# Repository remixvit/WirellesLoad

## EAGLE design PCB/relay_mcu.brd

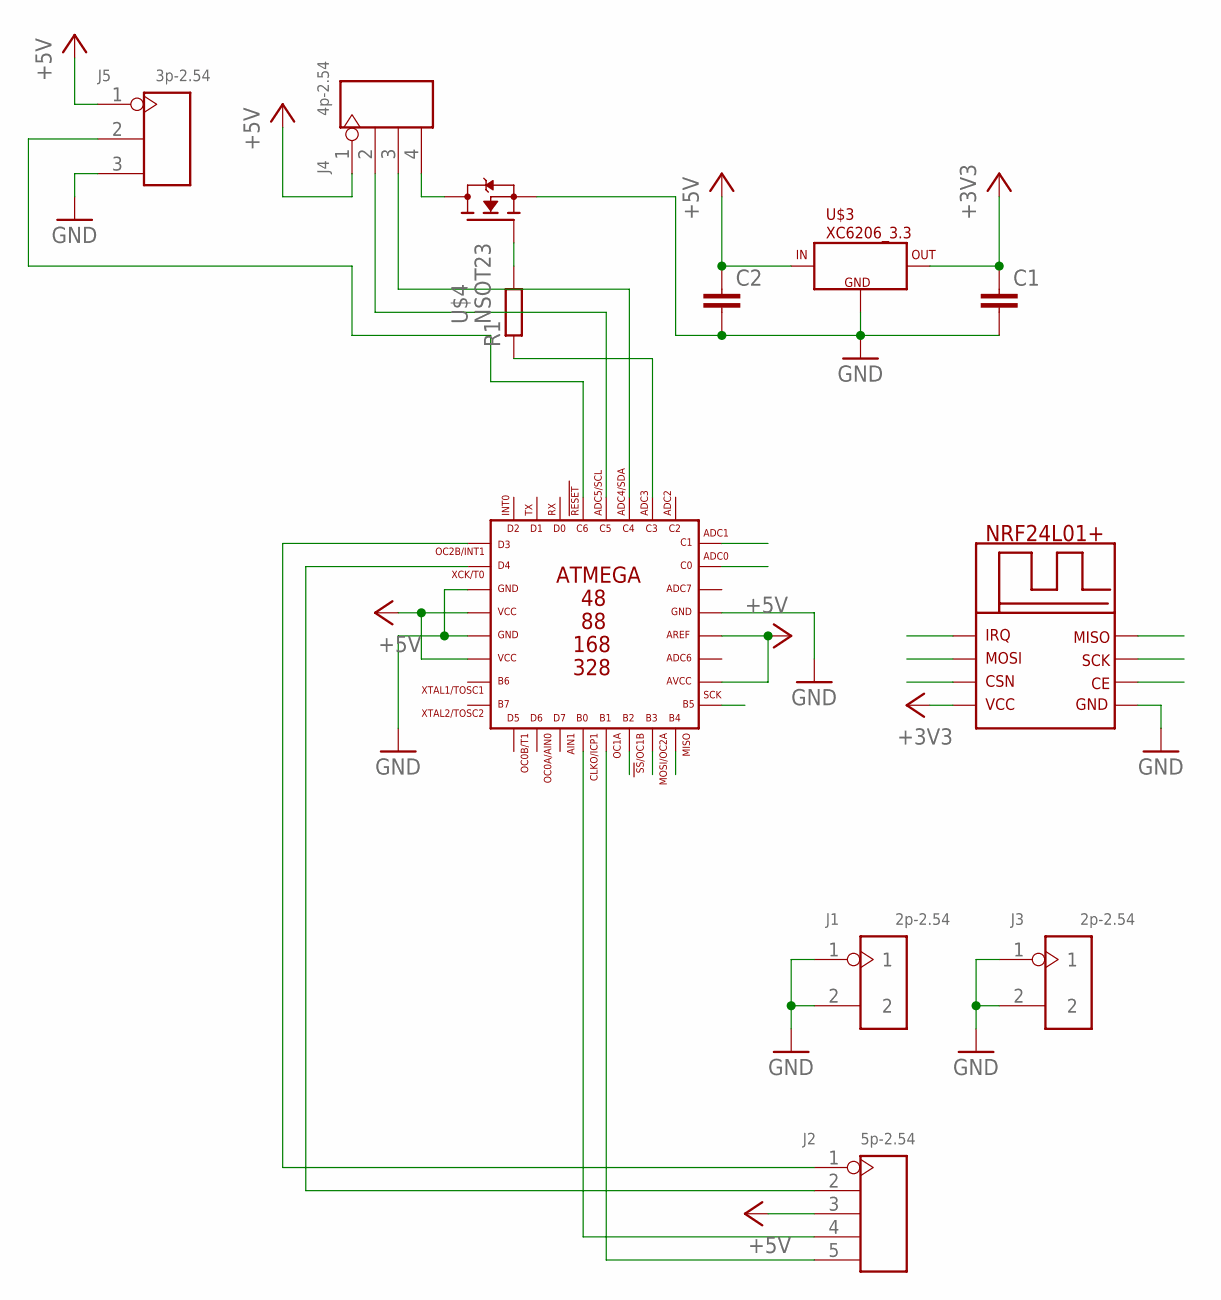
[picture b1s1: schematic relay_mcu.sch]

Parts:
C1, C2: C-EUC0805; C0805
J1, J3: 2p-2.54; H2-2.54
J2: 5p-2.54; H5-2.54
J4: 4p-2.54; H4-2.54
J5: 3p-2.54; H3-2.54
R1: R-EU_R0805; R0805
U$1: ATMEGAN8; TQFP32-08
U$2: NRF24; NRF
U$3: XC6206_3.3; SOT23
U$4: NSOT23; SOT23W

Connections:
+3V3: C1.1, U$2.VCC, U$3.2 (OUT)
+5V: J4.1, J5.1
CE: U$1.C1, U$2.CE
CSN: U$1.C0, U$2.CSN
GND: C1.2, C2.2, J1.1, J1.2, J3.1, J3.2, J5.3, U$1.GND, U$1.GND1, U$1.GND2, U$2.GND, U$3.1 (GND), U$4.S
IRQ: U$1.B2, U$2.IRQ
MISO: U$1.B4, U$2.MISO
MOSI: U$1.B3, U$2.MOSI
unnamed: C2.1, J2.3, U$1.AREF, U$1.AVCC, U$1.VCC, U$1.VCC1, U$3.3 (IN)
unnamed: J2.5, U$1.B1
unnamed: J2.4, U$1.B0
unnamed: J2.1, U$1.D3
unnamed: J2.2, U$1.D4
unnamed: J4.2, U$1.C5
unnamed: J4.3, U$1.C4
unnamed: J4.4, U$4.D
unnamed: R1.2, U$4.G
unnamed: R1.1, U$1.C3
unnamed: J5.2, U$1.C6
SCLK: U$1.B5, U$2.SCK

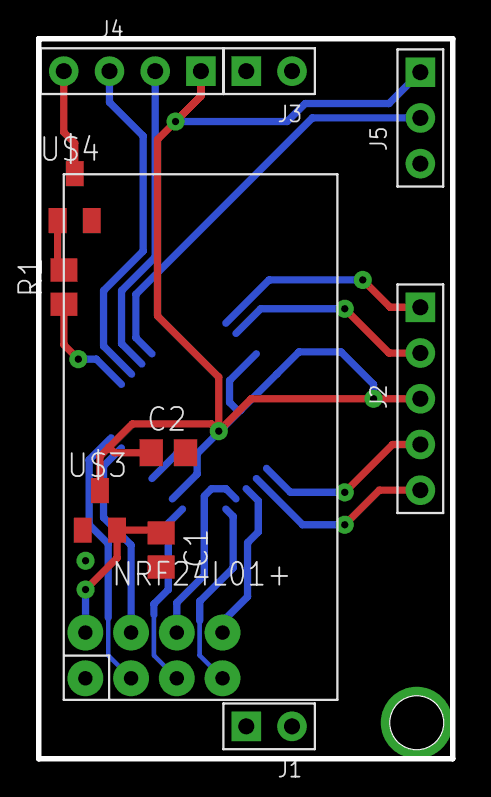
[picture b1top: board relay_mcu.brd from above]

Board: 2 copper layers, 23.0 x 40.0 mm, 12 parts (1 on the bottom side), 20 nets.

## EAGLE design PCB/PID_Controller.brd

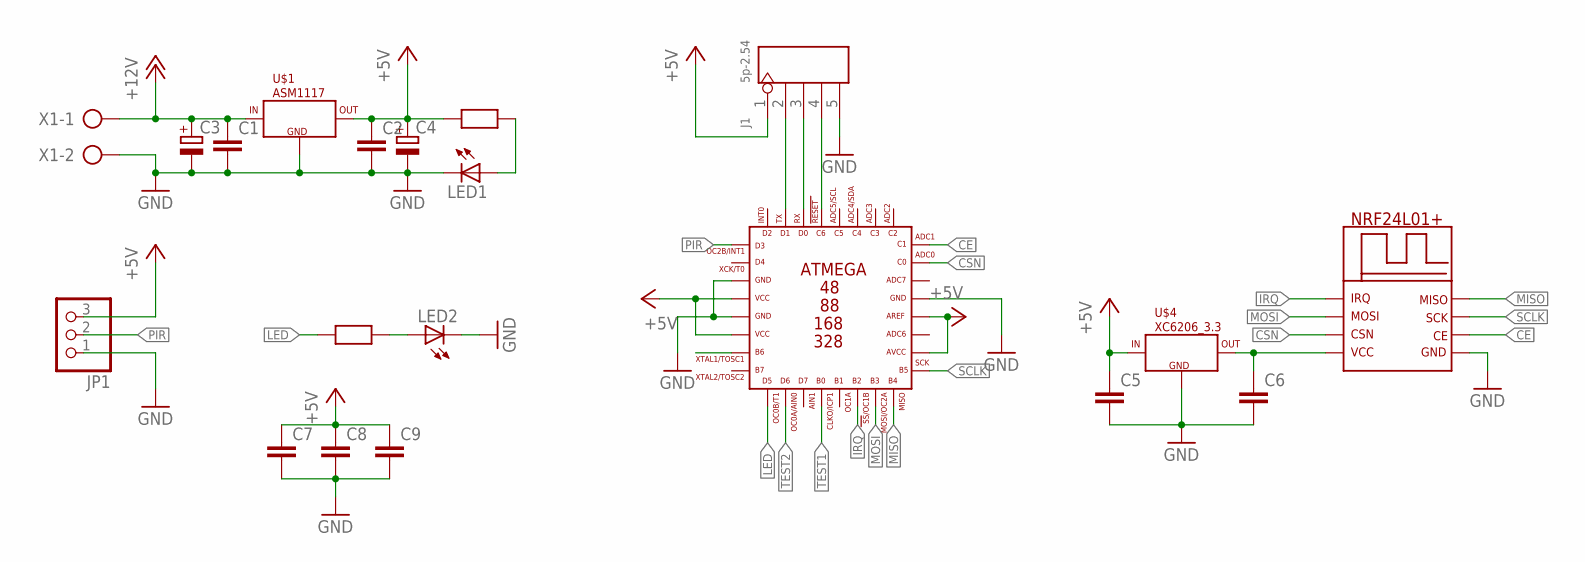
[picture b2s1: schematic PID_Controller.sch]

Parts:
C1, C2, C5, C6, C7, C8, C9: C-EUC0805; C0805
C3, C4: CPOL-EUE2.5-6; E2,5-6
J1: 5p-2.54; H5-2.54
JP1: PINHD-1X3; 1X03
LED1: LEDCHIP-LED0603; CHIP-LED0603
LED2: LED3MM
R1, R2: RES0603; R0603
U$1: ASM1117; SOT223
U$2: ATMEGAN8; TQFP32-08
U$3: NRF24; NRF
U$4: XC6206_3.3; SOT23
X1: AK500/2

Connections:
+5V: C2.1, C4.+, C5.1, C7.1, C8.1, C9.1, J1.1, JP1.3, R1.1, U$1.2 (OUT), U$1.4 (OUT), U$2.AREF, U$2.AVCC, U$2.VCC, U$2.VCC1, U$4.3 (IN)
+12V: C1.1, C3.+, U$1.3 (IN), X1.1
CE: U$2.C1, U$3.CE
CSN: U$2.C0, U$3.CSN
GND: C1.2, C2.2, C3.-, C4.-, C5.2, C6.2, C7.2, C8.2, C9.2, J1.5, JP1.1, LED1.C, LED2.K (C), U$1.1 (GND), U$2.GND, U$2.GND1, U$2.GND2, U$3.GND, U$4.1 (GND), X1.2
IRQ: U$2.B2, U$3.IRQ
LED: R2.1, U$2.D5
MISO: U$2.B4, U$3.MISO
MOSI: U$2.B3, U$3.MOSI
unnamed: LED1.A, R1.2
unnamed: J1.2, U$2.D1
unnamed: J1.3, U$2.D0
unnamed: J1.4, U$2.C6
unnamed: C6.1, U$3.VCC, U$4.2 (OUT)
unnamed: LED2.A, R2.2
PIR: JP1.2, U$2.D3
SCLK: U$2.B5, U$3.SCK
TEST1: U$2.B0
TEST2: U$2.D6

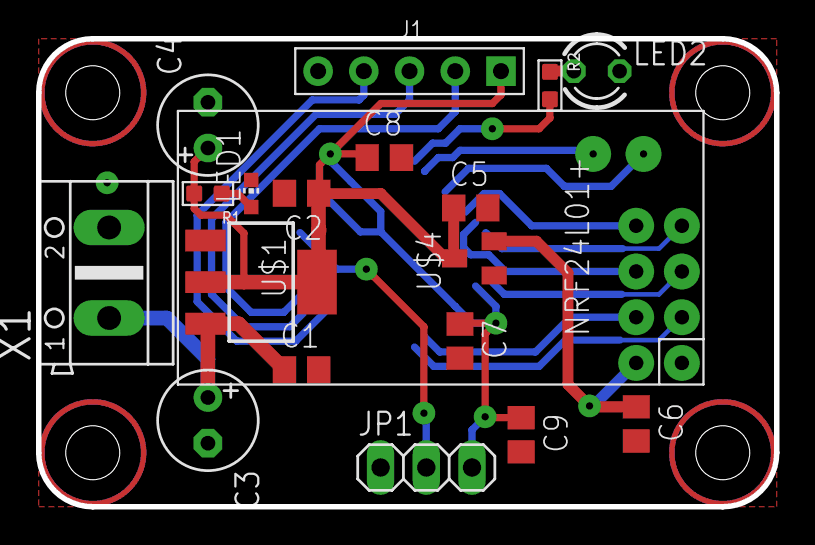
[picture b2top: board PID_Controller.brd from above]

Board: 2 copper layers, 41.0 x 26.0 mm, 20 parts (1 on the bottom side), 17 nets.

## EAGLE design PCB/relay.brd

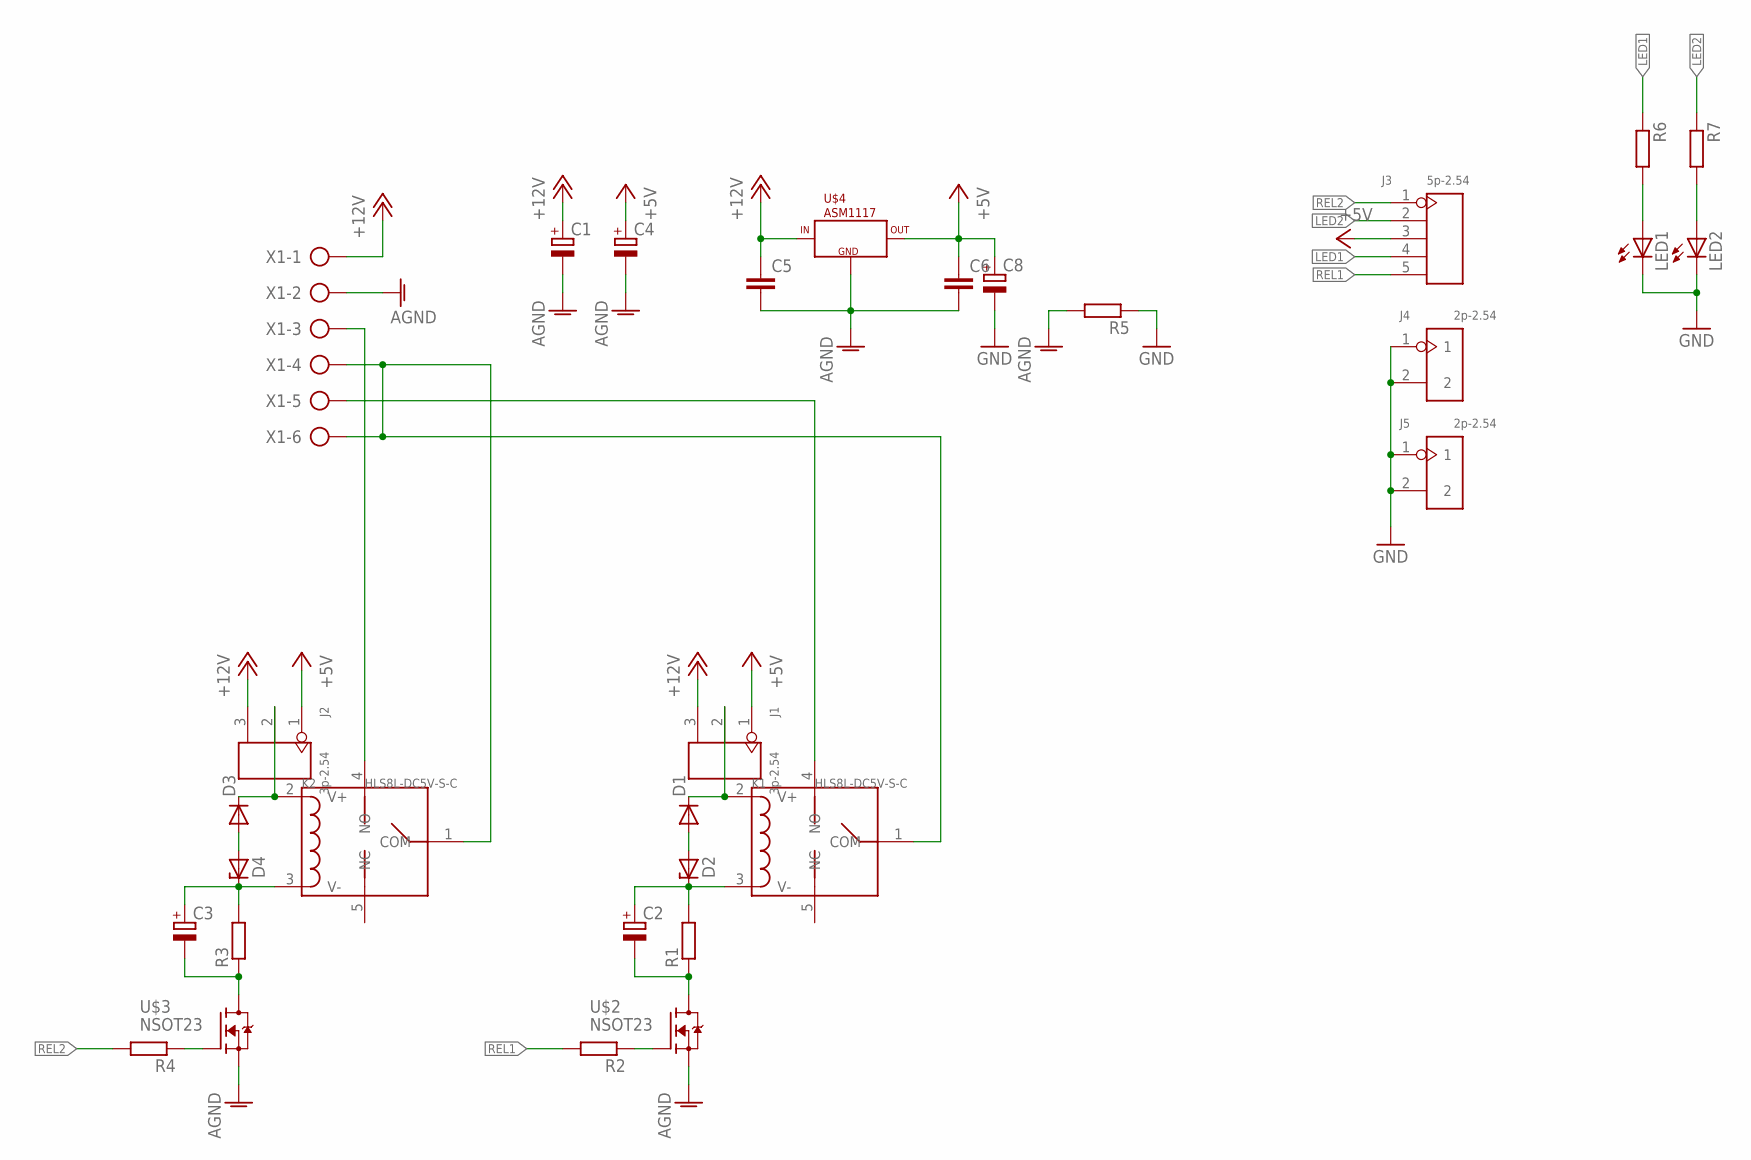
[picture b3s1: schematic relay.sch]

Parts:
C1, C2, C3, C4: CPOL-EU153CLV-0405; 153CLV-0405
C5, C6: C-EUC0805; C0805
C8: CPOL-EUSMCD; SMC_D
D1, D3: DIODE-MINIMELF; MINIMELF
D2, D4: ZENER-DIODESOD80C; SOD80C
J1, J2: 3p-2.54; H3-2.54
J3: 5p-2.54; H5-2.54
J4, J5: 2p-2.54; H2-2.54
K1, K2: HLS8L-DC5V-S-C; REY5-19.0X15.0X15.0MM
LED1, LED2: LED5MM
R1, R2, R3, R4, R5, R6, R7: R-EU_R0805; R0805
U$2, U$3: NSOT23; SOT23W
U$4: ASM1117; SOT223
X1: AK500/6-H

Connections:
+5V: C4.+, C6.1, C8.+, J1.1, J2.1, J3.3, U$4.2 (OUT), U$4.4 (OUT)
+12V: C1.+, C5.1, J1.3, J2.3, U$4.3 (IN), X1.1
AGND: C1.-, C4.-, C5.2, C6.2, R5.2, U$2.S, U$3.S, U$4.1 (GND), X1.2
GND: C8.-, J4.1, J4.2, J5.1, J5.2, LED1.K (C), LED2.K (C), R5.1
LED1: J3.4, R6.1
LED2: J3.2, R7.1
unnamed: D1.C, J1.2, K1.2 (V+)
unnamed: C2.+, D2.C, K1.3 (V-), R1.2
unnamed: D1.A, D2.A
unnamed: C2.-, R1.1, U$2.D
unnamed: R2.1, U$2.G
unnamed: K1.4 (NO), X1.5
unnamed: D3.C, J2.2, K2.2 (V+)
unnamed: C3.+, D4.C, K2.3 (V-), R3.2
unnamed: D3.A, D4.A
unnamed: C3.-, R3.1, U$3.D
unnamed: R4.1, U$3.G
unnamed: LED1.A, R6.2
unnamed: K1.1 (COM), K2.1 (COM), X1.4, X1.6
unnamed: LED2.A, R7.2
unnamed: K2.4 (NO), X1.3
REL1: J3.5, R2.2
REL2: J3.1, R4.2

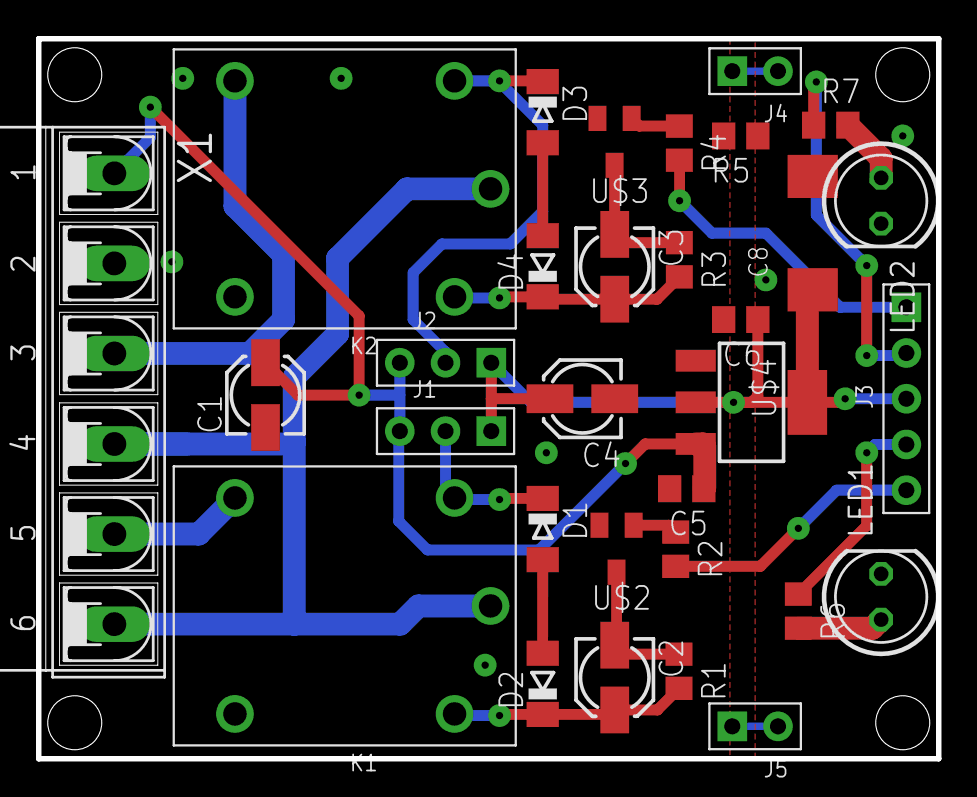
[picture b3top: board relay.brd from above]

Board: 2 copper layers, 50.0 x 40.0 mm, 31 parts (0 on the bottom side), 23 nets.

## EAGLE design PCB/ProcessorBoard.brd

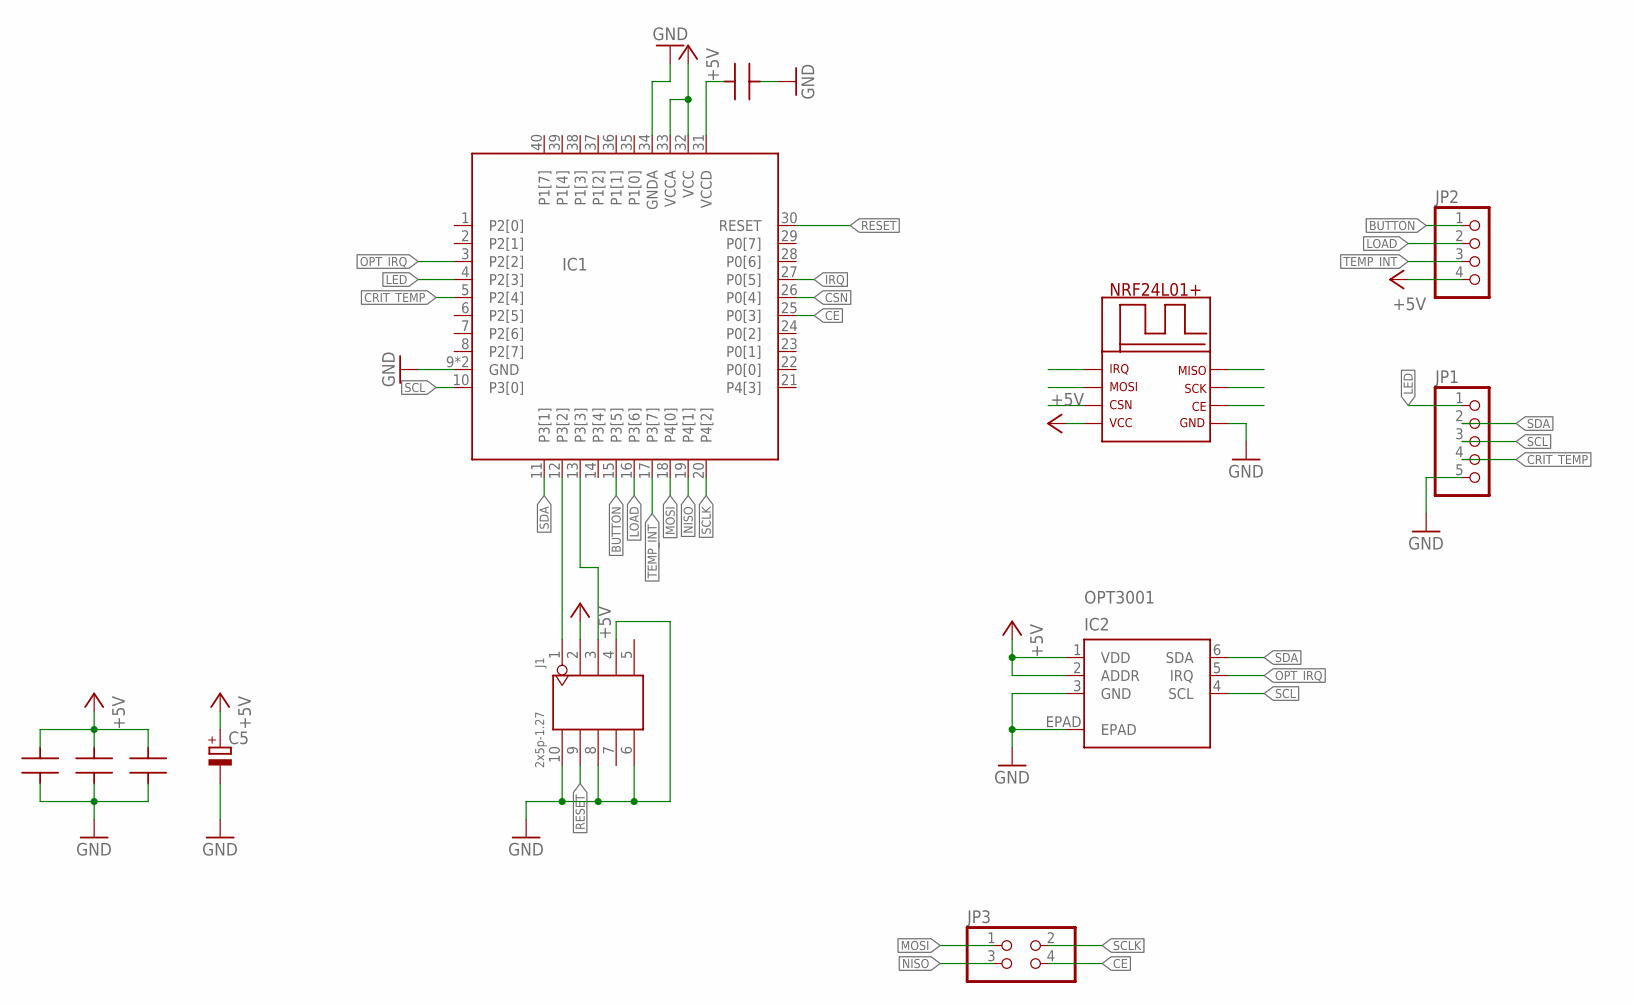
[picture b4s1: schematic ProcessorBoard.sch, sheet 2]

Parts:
C1, C2, C3, C4: CAP0603; C0603
C5: CPOL-EUSMCA; SMC_A
IC1: CY8C4245-LQI-LONG; QFN40-LONG
IC2: OPT3001; USON6
J1: 2x5p-1.27; H2X5-SMD-1.27
JP1: PINHD-1X5; 1X05
JP2: PINHD-1X4; 1X04
JP3: PINHD-2X2; 2X02
U$1: NRF24; NRF

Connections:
+5V: C2.2, C3.2, C4.2, C5.+, IC1.32 (VCC), IC1.33 (VCCA), IC2.1 (VDD), IC2.2 (ADDR), J1.2, JP2.4, U$1.VCC
BUTTON: IC1.15 (P3[5]), JP2.1
CE: IC1.25 (P0[3]), JP3.4, U$1.CE
CRIT_TEMP: IC1.5 (P2[4]), JP1.4
CSN: IC1.26 (P0[4]), U$1.CSN
GND: C1.2, C2.1, C3.1, C4.1, C5.-, IC1.9 (GND), IC1.34 (GNDA), IC1.41 (GND), IC2.3 (GND), IC2.EPAD, J1.4, J1.6, J1.8, J1.10, JP1.5, U$1.GND
IRQ: IC1.27 (P0[5]), U$1.IRQ
LED: IC1.4 (P2[3]), JP1.1
LOAD: IC1.16 (P3[6]), JP2.2
MOSI: IC1.18 (P4[0]), JP3.1, U$1.MOSI
unnamed: IC1.12 (P3[2]), J1.1
unnamed: C1.1, IC1.31 (VCCD)
unnamed: IC1.13 (P3[3]), J1.3
NISO: IC1.19 (P4[1]), JP3.3, U$1.MISO
OPT_IRQ: IC1.3 (P2[2]), IC2.5 (IRQ)
RESET: IC1.30 (RESET), J1.9
SCL: IC1.10 (P3[0]), IC2.4 (SCL), JP1.3
SCLK: IC1.20 (P4[2]), JP3.2, U$1.SCK
SDA: IC1.11 (P3[1]), IC2.6 (SDA), JP1.2
TEMP_INT: IC1.17 (P3[7]), JP2.3

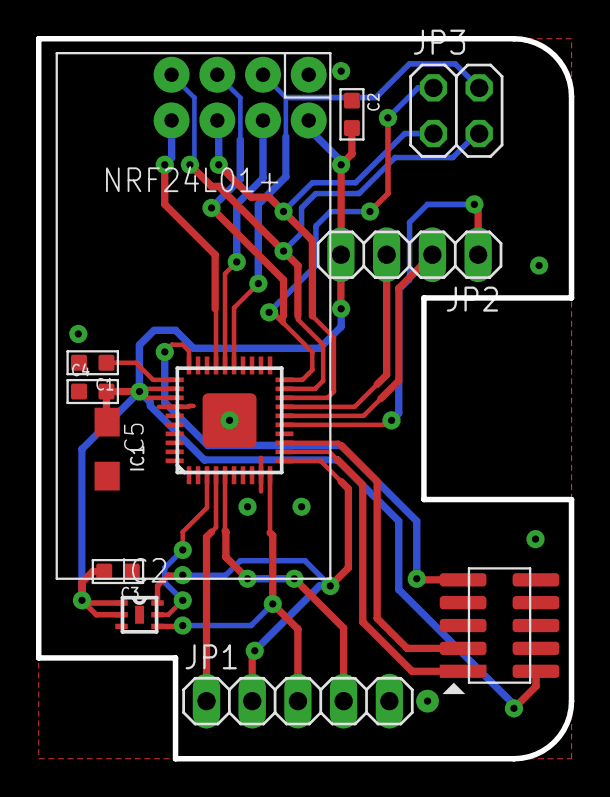
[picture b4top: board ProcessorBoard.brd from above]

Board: 2 copper layers, 29.6 x 40.0 mm, 12 parts (0 on the bottom side), 20 nets.

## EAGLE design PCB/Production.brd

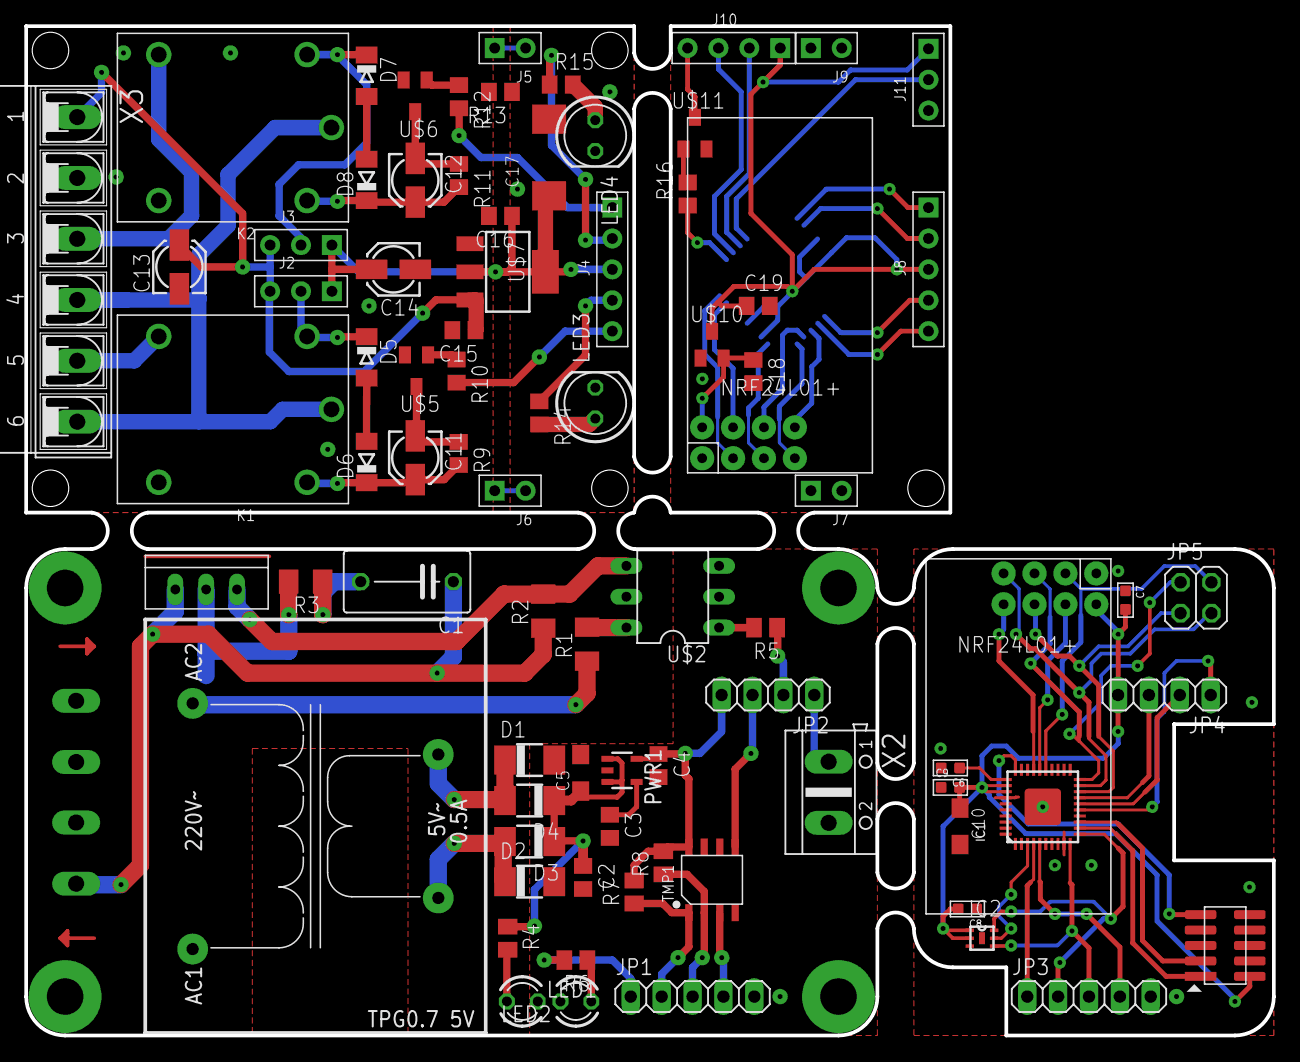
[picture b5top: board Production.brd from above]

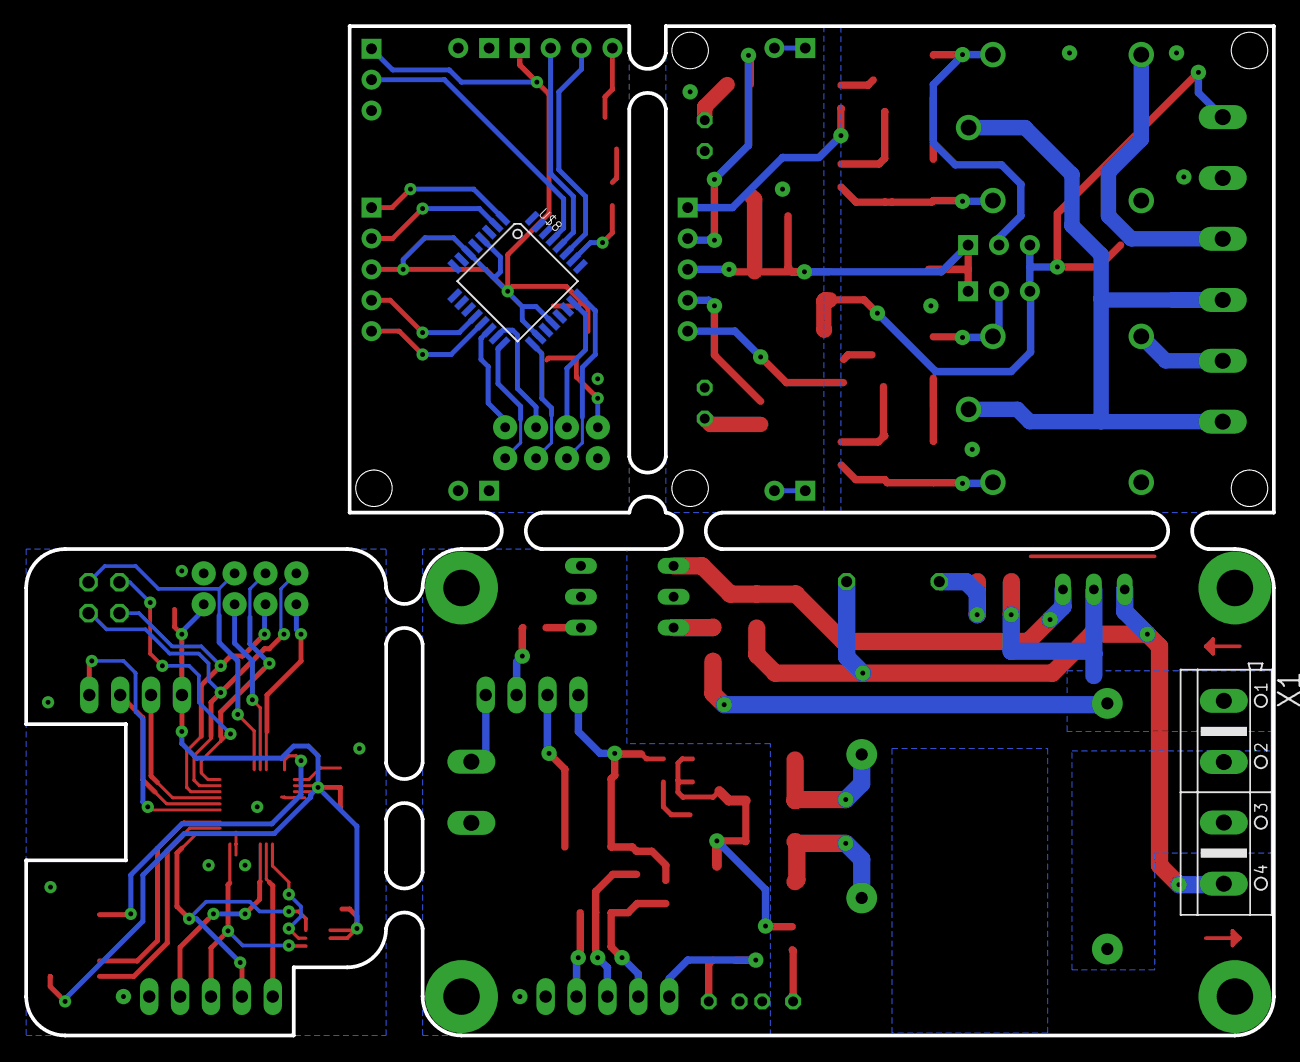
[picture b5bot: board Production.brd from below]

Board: 2 copper layers, 102.6 x 83.0 mm, 83 parts (2 on the bottom side), 85 nets.

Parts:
C1: C075-052X106
C2, C3, C4, C15, C16, C18, C19: C0805
C5, C10: SMC_A
C6, C7, C8, C9: C0603
C11, C12, C13, C14: 153CLV-0405
C17: SMC_D
D1, D2, D3, D4: DO-214AC
D5, D7: MINIMELF
D6, D8: SOD80C
IC1: CY8C4245-LQI-LONG; QFN40-LONG
IC2: OPT3001; USON6
J1: 2x5p-1.27; H2X5-SMD-1.27
J2, J3, J11: 3p-2.54; H3-2.54
J4, J8: 5p-2.54; H5-2.54
J5, J6, J7, J9: 2p-2.54; H2-2.54
J10: 4p-2.54; H4-2.54
JP1, JP3: 1X05
JP2, JP4: 1X04
JP5: 2X02
K1, K2: HLS8L-DC5V-S-C; REY5-19.0X15.0X15.0MM
LED1, LED2: LED3MM
LED3, LED4: LED5MM
PWR1: LP2992; SOT23-5
R1, R2, R3: M1206
R4, R5, R6, R7, R8: M0805
R9, R10, R11, R12, R13, R14, R15, R16: R0805
TMP1: LM92; SOIC8-1.27-5X4MM
U$1: ТПГ-0.7-5V; TPG-0.7-5V
U$2: MOC3043; DIL06
U$3: BTB16; TO220NORM
U$4, U$9: NRF24; NRF
U$5, U$6, U$11: NSOT23; SOT23W
U$7: ASM1117; SOT223
U$8: ATMEGAN8; TQFP32-08
U$10: XC6206_3.3; SOT23
X1: AK500/4
X2: AK500/2
X3: AK500/6-H

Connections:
+3V3: C18.1, U$9.VCC, U$10.2
+5V: C4.1, JP2.4, PWR1.5, R7.2, R8.2, TMP1.8
+5V1: C7.2, C8.2, C9.2, C10.+, IC1.32, IC1.33, IC2.1, IC2.2, J1.2, JP4.4, U$4.VCC
+5V2: C14.+, C16.1, C17.+, J2.1, J3.1, J4.3, U$7.2, U$7.4
+5V3: J10.1, J11.1
+12V: C13.+, C15.1, J2.3, J3.3, U$7.3, X3.1
AGND: C13.-, C14.-, C15.2, C16.2, R13.2, U$5.S, U$6.S, U$7.1, X3.2
BUTTON: IC1.15, JP4.1
CE: IC1.25, JP5.4, U$4.CE
CE1: U$8.C1, U$9.CE
CRIT_TEMP: IC1.5, JP3.4
CSN: IC1.26, U$4.CSN
CSN1: U$8.C0, U$9.CSN
GND: C2.2, C3.2, C4.2, C5.-, D1.A, D2.A, JP1.5, LED1.K, LED2.K, PWR1.2, TMP1.4, TMP1.6, TMP1.7, U$2.2, X2.2
GND1: C6.2, C7.1, C8.1, C9.1, C10.-, IC1.9, IC1.34, IC1.41, IC2.3, IC2.EPAD, J1.4, J1.6, J1.8, J1.10, JP3.5, U$4.GND
GND2: C17.-, J5.1, J5.2, J6.1, J6.2, LED3.K, LED4.K, R13.1
GND3: C18.2, C19.2, J7.1, J7.2, J9.1, J9.2, J11.3, U$8.GND, U$8.GND1, U$8.GND2, U$9.GND, U$10.1, U$11.S
IRQ: IC1.27, U$4.IRQ
IRQ1: U$8.B2, U$9.IRQ
LED: IC1.4, JP3.1
LED1: J4.4, R14.1
LED2: J4.2, R15.1
LOAD: JP2.2, R5.1
LOAD1: IC1.16, JP4.2
MISO: U$8.B4, U$9.MISO
MOSI: IC1.18, JP5.1, U$4.MOSI
MOSI1: U$8.B3, U$9.MOSI
unnamed: U$1.AC1, X1.2, X1.3
unnamed: R1.1, R3.2, U$1.AC2, U$3.MT2, X1.1
unnamed: D1.C, D4.A, U$1.DC2
unnamed: D2.C, D3.A, U$1.DC1
unnamed: R1.2, U$2.6
unnamed: R2.2, U$2.4, U$3.GATE
unnamed: C1.1, R2.1, U$3.MT1, X1.4
unnamed: C1.2, R3.1
unnamed: LED1.A, R4.2
unnamed: R5.2, U$2.1
unnamed: C3.1, PWR1.4
unnamed: JP1.1, R6.2
unnamed: LED2.A, R6.1
unnamed: JP1.2, R7.1, TMP1.1
unnamed: JP1.3, R8.1, TMP1.2
unnamed: JP1.4, TMP1.3
unnamed: JP2.1, X2.1
unnamed: C6.1, IC1.31
unnamed: IC1.12, J1.1
unnamed: IC1.13, J1.3
unnamed: D5.C, J2.2, K1.2
unnamed: C11.+, D6.C, K1.3, R9.2
unnamed: D5.A, D6.A
unnamed: C11.-, R9.1, U$5.D
unnamed: R10.1, U$5.G
unnamed: D7.C, J3.2, K2.2
unnamed: C12.+, D8.C, K2.3, R11.2
unnamed: D7.A, D8.A
unnamed: C12.-, R11.1, U$6.D
unnamed: R12.1, U$6.G
unnamed: K1.4, X3.5
unnamed: K1.1, K2.1, X3.4, X3.6
unnamed: K2.4, X3.3
unnamed: LED3.A, R14.2
unnamed: LED4.A, R15.2
unnamed: C19.1, J8.3, U$8.AREF, U$8.AVCC, U$8.VCC, U$8.VCC1, U$10.3
unnamed: J8.5, U$8.B1
unnamed: J8.4, U$8.B0
unnamed: J8.1, U$8.D3
unnamed: J8.2, U$8.D4
unnamed: J10.2, U$8.C5
unnamed: J10.3, U$8.C4
unnamed: J10.4, U$11.D
unnamed: R16.2, U$11.G
unnamed: R16.1, U$8.C3
unnamed: J11.2, U$8.C6
NISO: IC1.19, JP5.3, U$4.MISO
OPT_IRQ: IC1.3, IC2.5
REL1: J4.5, R10.2
REL2: J4.1, R12.2
RESET: IC1.30, J1.9
SCL: IC1.10, IC2.4, JP3.3
SCLK: IC1.20, JP5.2, U$4.SCK
SCLK1: U$8.B5, U$9.SCK
SDA: IC1.11, IC2.6, JP3.2
TEMP_INT: JP2.3, TMP1.5
TEMP_INT1: IC1.17, JP4.3
VCC: C2.1, C5.+, D3.C, D4.C, PWR1.1, PWR1.3, R4.1

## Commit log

2015-11-23 Create PCB Layout
2015-11-23 File Manegment
2015-11-23 Del Copies
2015-11-24 Создал проект для CY8C4245LQI
2015-11-24 Add i2c & spi block in project
2015-11-24 Назначил выводы микроконтроллера. Подключил внешнее прерывание
2015-11-24 Подключи диспетчер задач, библиотеку: OPT3001
2015-12-14 Add new board for Power Controll WiFi Router
